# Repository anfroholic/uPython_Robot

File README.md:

Temporary home for a browser based serial terminal can be found here https://anfroholic.github.io/stache-terminal/

# Mo is live on Kickstarter!
Find more here https://www.kickstarter.com/projects/1474681136/mo-the-most-magnificent-mustached-machine 

We are the Mechanical Mustaches
FIRST® Robotics Team 8122

this is Mo the mini_mustache robotic car

Mo Dance for the FIRST Time!

Mo designed by our very own Olivia

Coming soon! Carl the Controller

here is a race put on by our amazing lead progammer Angie!!

Still in development but some previews are:

Mo hosts webpages to edit himself
## Homepage

## Live coding REPL like code terminal

## Stachboard
Dashboard is autopopulated with motors, servos, agents and many other inputs and outputs that are created

## Mo also has an editor where you can edit your own code

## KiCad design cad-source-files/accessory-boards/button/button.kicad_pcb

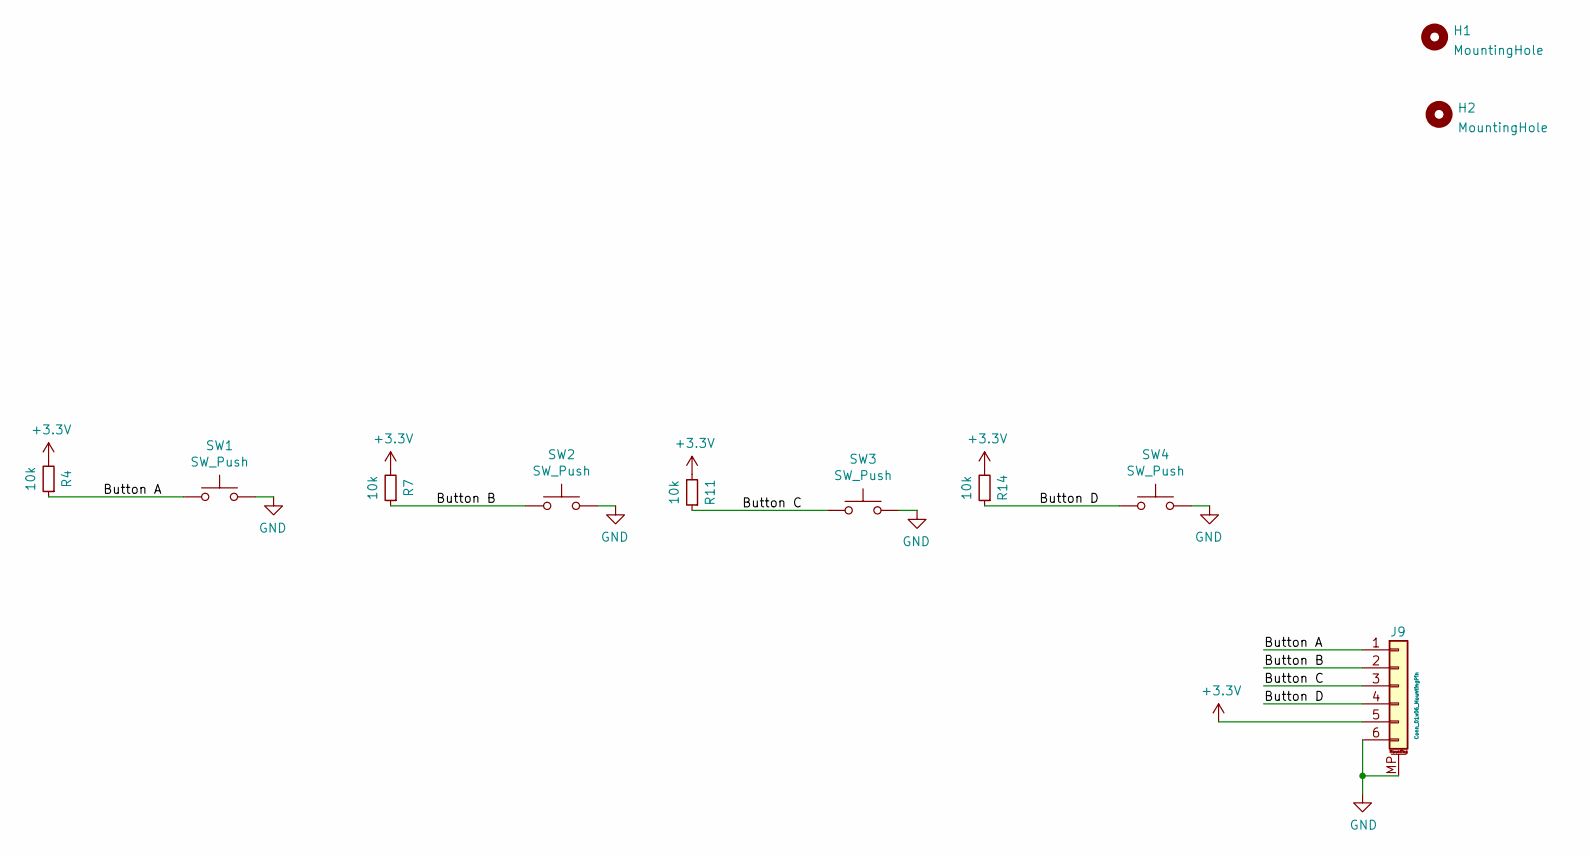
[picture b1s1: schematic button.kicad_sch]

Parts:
H1, H2: MountingHole; MountingHole_3.2mm_M3_ISO14580
J9: Conn_01x06_MountingPin; TE_84952-6_1x06-1MP_P1.0mm_Horizontal
R4, R7, R11, R14: 10k; R_0603_1608Metric
SW1, SW2, SW3, SW4: SW_Push; SWITCH_2x3_SMD_TACTILE_GREEN

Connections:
+3V3: J9.5, R4.2, R7.2, R11.2, R14.2
/Button A: J9.1, R4.1, SW1.1
/Button B: J9.2, R7.1, SW2.1
/Button C: J9.3, R11.1, SW3.1
/Button D: J9.4, R14.1, SW4.1
GND: J9.6, J9.MP (MountPin), SW1.2, SW2.2, SW3.2, SW4.2

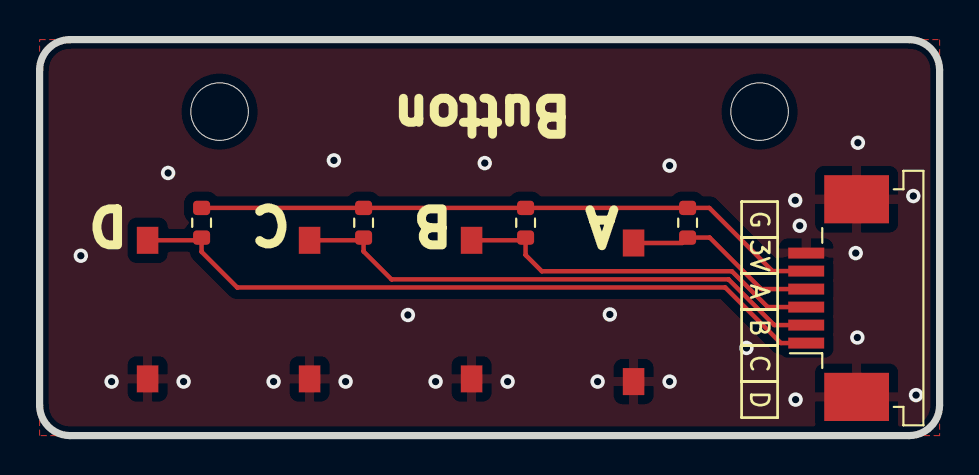
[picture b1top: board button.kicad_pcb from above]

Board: 2 copper layers, 50.0 x 22.0 mm, 11 parts (0 on the bottom side), 6 nets.

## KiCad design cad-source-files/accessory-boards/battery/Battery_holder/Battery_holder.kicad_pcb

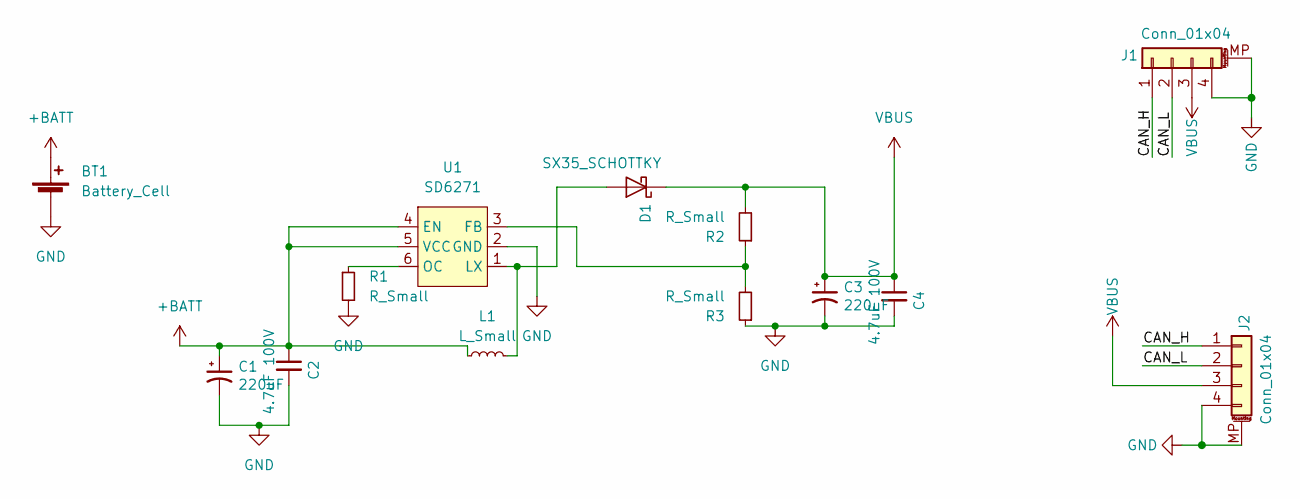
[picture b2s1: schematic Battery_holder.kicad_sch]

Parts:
BT1: Battery_Cell; 18650_holder
C1, C3: 220uF; CP_Elec_10x10.5
C2, C4: 4.7uF 100V; C_0805_2012Metric
D1: SX35_SCHOTTKY; D_SMA
J1, J2: Conn_01x04; JST_PH_S4B-PH-SM4-TB_1x04-1MP_P2.00mm_Horizontal
L1: L_Small; INDUCTOR_4.7uH_SMALL
R1, R2, R3: R_Small; R_0603_1608Metric
U1: SD6271; SOT-23-6

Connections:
+BATT: BT1.1 (+), C1.1, C2.1, L1.1, U1.4 (EN), U1.5 (VCC)
/CAN_H: J1.1, J2.1
/CAN_L: J1.2, J2.2
GND: BT1.2 (-), C1.2, C2.2, C3.2, C4.2, J1.4, J1.MP (MountPin), J2.4, J2.MP (MountPin), R1.2, R3.1, U1.2 (GND)
unnamed: D1.2 (A), L1.2, U1.1 (LX)
unnamed: R2.1, R3.2, U1.3 (FB)
unnamed: R1.1, U1.6 (OC)
VBUS: C3.1, C4.1, D1.1 (K), J1.3, J2.3, R2.2

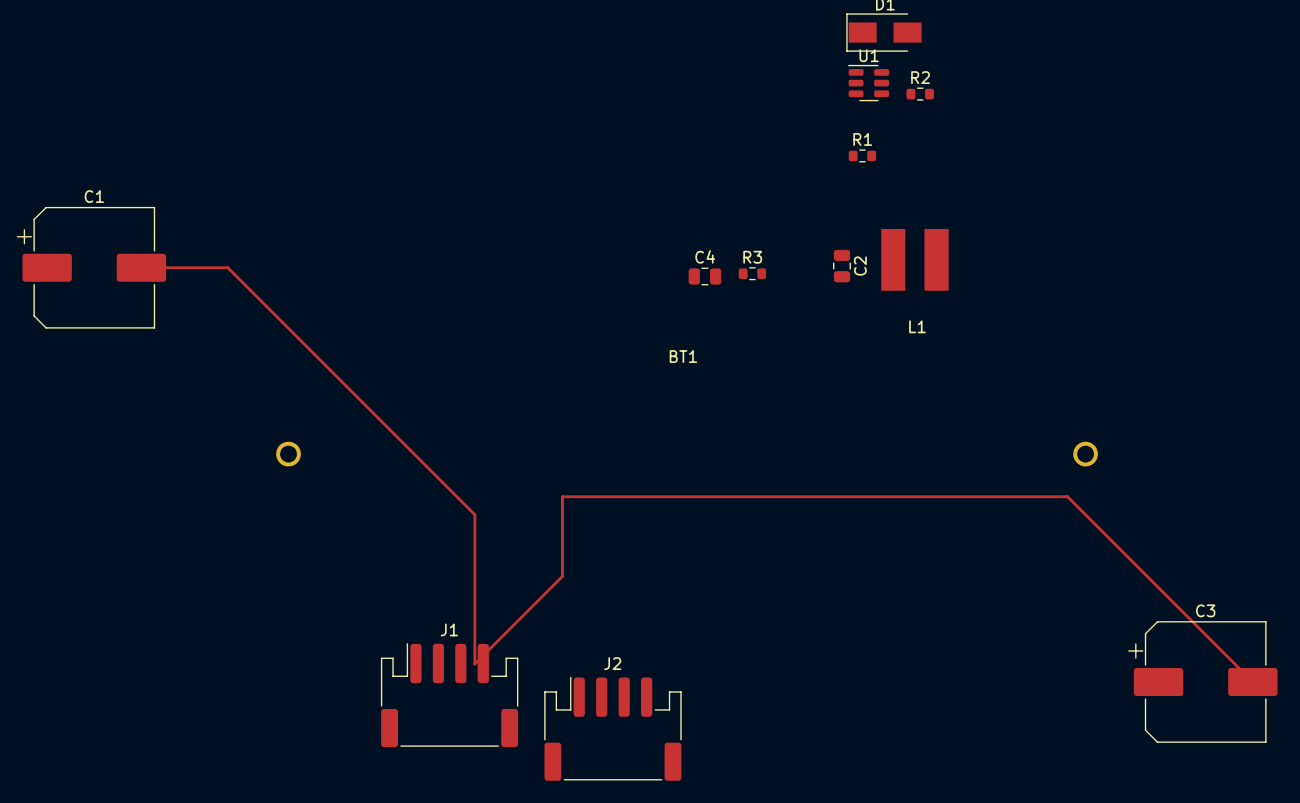
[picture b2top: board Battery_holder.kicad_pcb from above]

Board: 2 copper layers, 13 parts (0 on the bottom side), 8 nets.

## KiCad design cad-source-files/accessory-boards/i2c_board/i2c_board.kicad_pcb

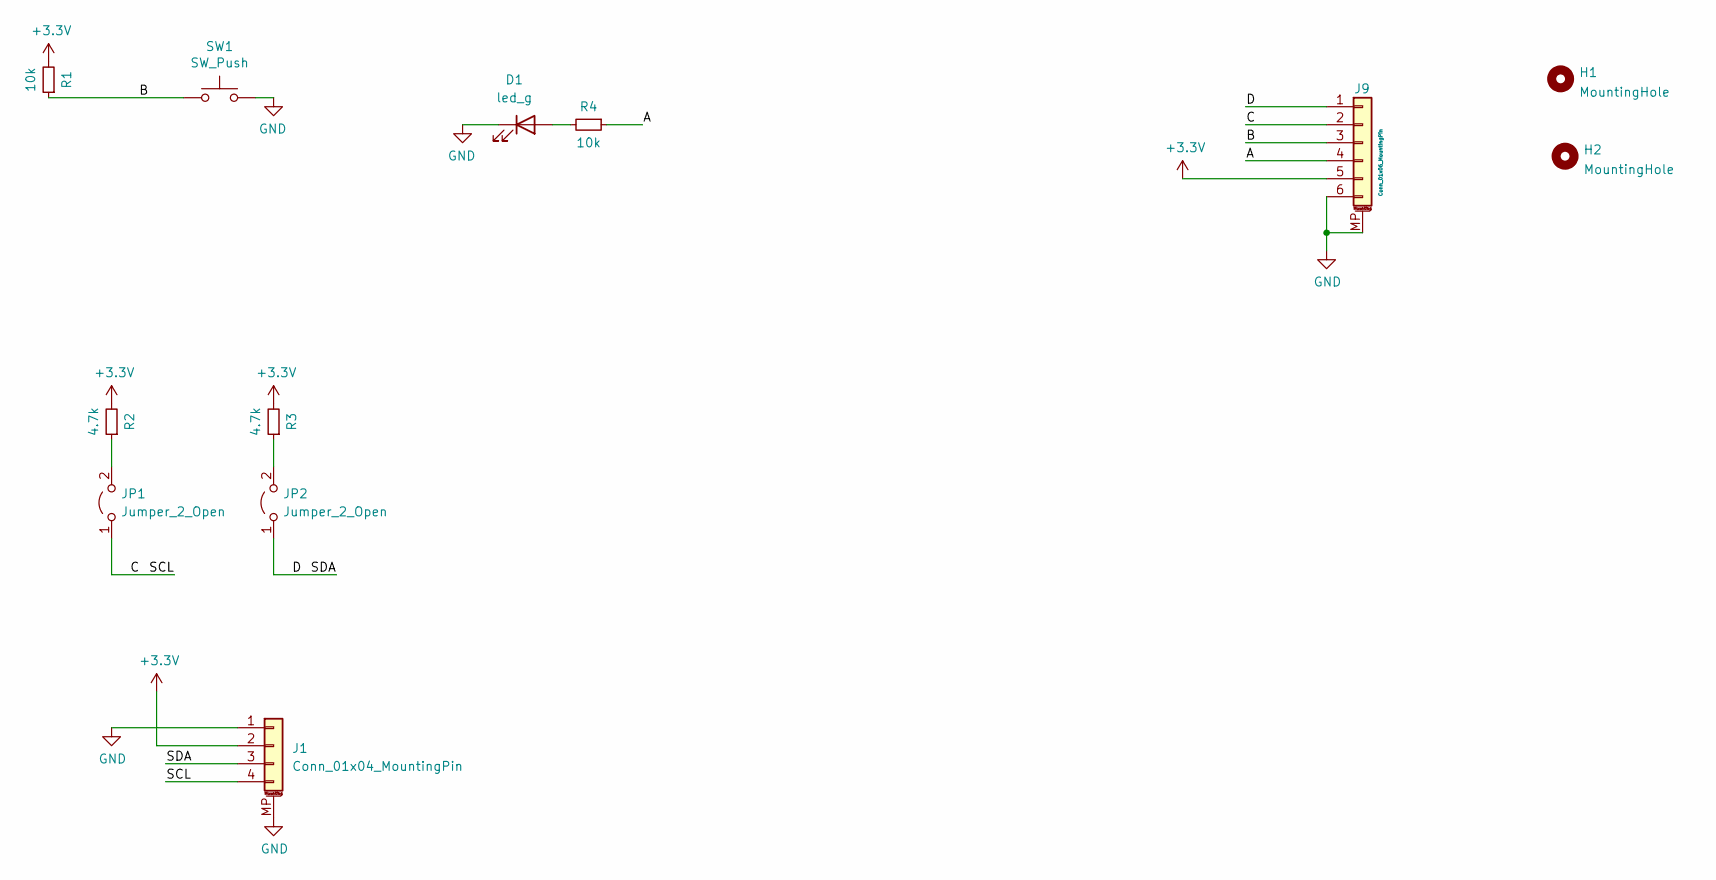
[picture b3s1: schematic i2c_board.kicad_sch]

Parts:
D1: led_g; LED_0603_1608Metric
H1, H2: MountingHole; MountingHole_3.2mm_M3_ISO14580
J1: Conn_01x04_MountingPin; JST_SH_SM04B-SRSS-TB_1x04-1MP_P1.00mm_Horizontal
J9: Conn_01x06_MountingPin; TE_84952-6_1x06-1MP_P1.0mm_Horizontal
JP1, JP2: Jumper_2_Open; SolderJumper-2_P1.3mm_Bridged_RoundedPad1.0x1.5mm
R1, R4: 10k; R_0603_1608Metric
R2, R3: 4.7k; R_0603_1608Metric
SW1: SW_Push; SWITCH_2x3_SMD_TACTILE_GREEN

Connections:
+3V3: J1.2, J9.5, R1.2, R2.2, R3.2
/A: J9.4, R4.1
/B: J9.3, R1.1, SW1.1
/C: J1.4, J9.2, JP1.1 (A)
/D: J1.3, J9.1, JP2.1 (A)
GND: D1.1 (K), J1.1, J1.MP (MountPin), J9.6, J9.MP (MountPin), SW1.2
unnamed: D1.2 (A), R4.2
unnamed: JP1.2 (B), R2.1
unnamed: JP2.2 (B), R3.1

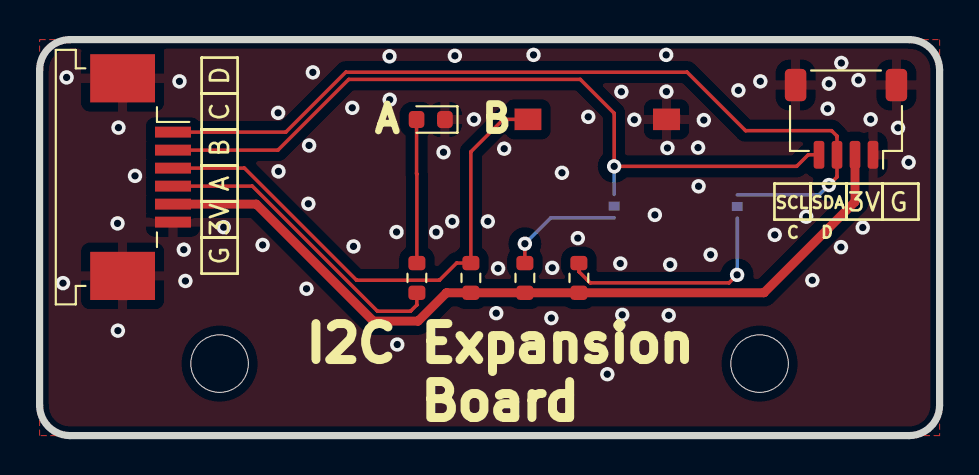
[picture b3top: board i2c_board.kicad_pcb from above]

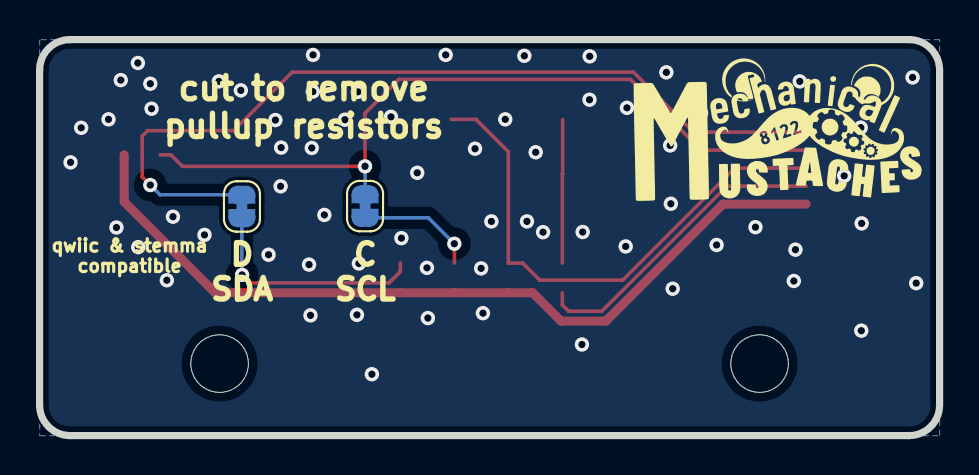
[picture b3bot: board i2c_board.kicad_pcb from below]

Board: 2 copper layers, 50.0 x 22.0 mm, 12 parts (2 on the bottom side), 9 nets.

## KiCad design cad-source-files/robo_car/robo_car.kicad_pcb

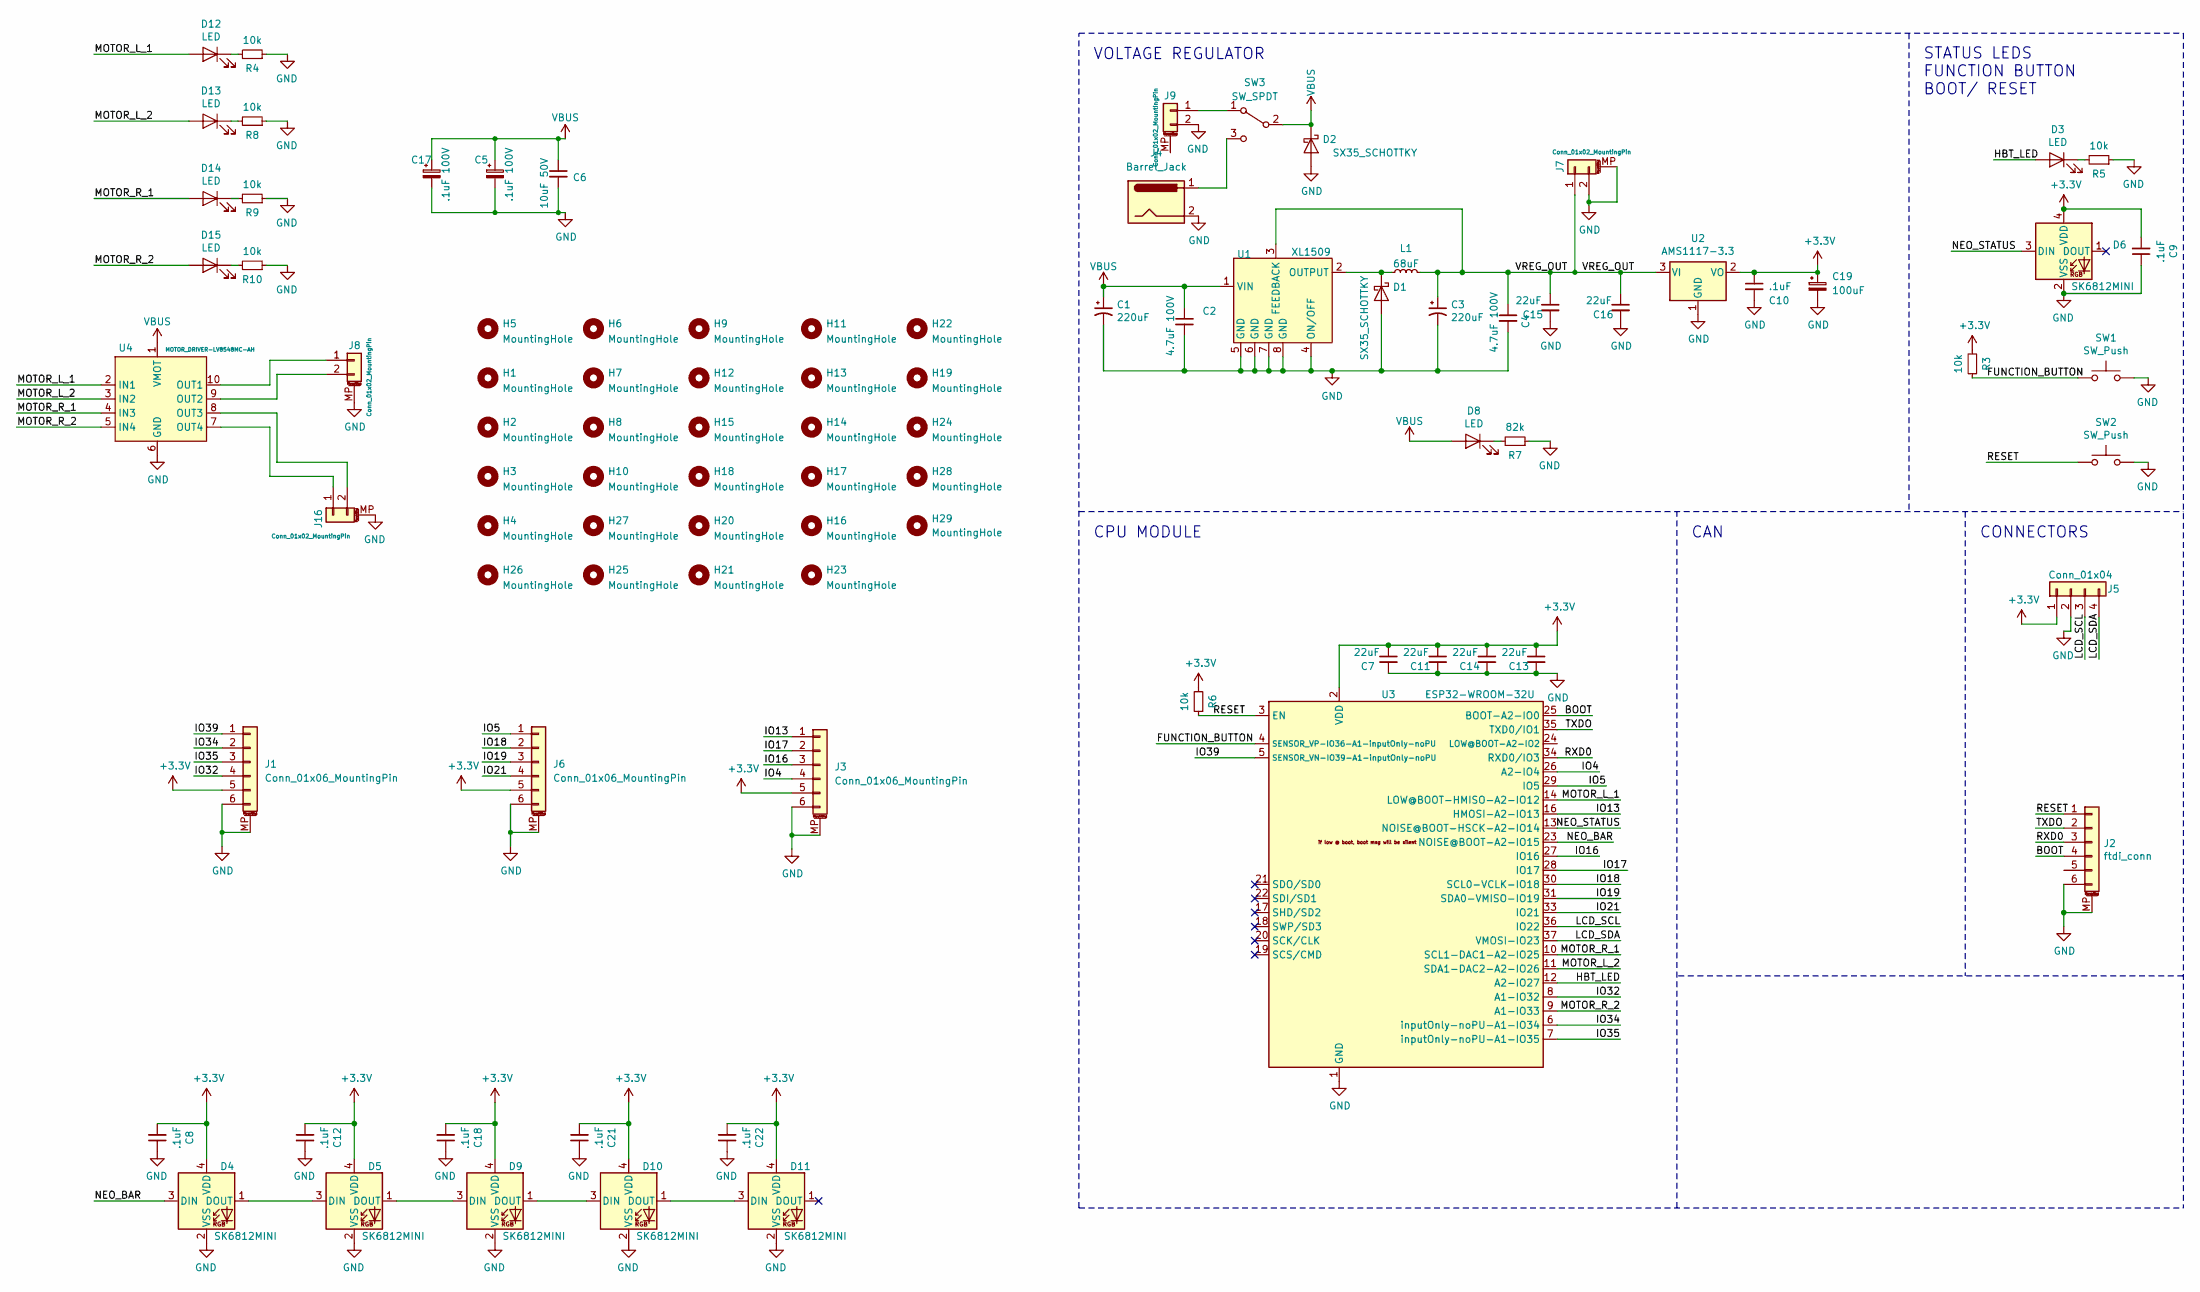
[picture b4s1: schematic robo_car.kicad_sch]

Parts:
C1, C3: 220uF; CP_Elec_10x10.5
C2, C4: 4.7uF 100V; C_0805_2012Metric
C5, C17: .1uF 100V; C_0805_2012Metric
C6: 10uF 50V; C_1206_3216Metric
C7, C11, C13, C14, C15, C16: 22uF; C_0805_2012Metric
C8, C9, C10, C12, C18, C21, C22: .1uF; C_0603_1608Metric
C19: 100uF; CP_EIA-3528-21_Kemet-B
D1, D2: SX35_SCHOTTKY; D_SMA
D3, D8, D12, D13, D14, D15: LED; LED_0603_1608Metric
D4, D5, D6, D9, D10, D11: SK6812MINI; LED_SK6812MINI_PLCC4_3.5x3.5mm_P1.75mm
H1, H2, H3, H4, H5, H6, H7, H8, H9, H10, H11, H12, H13, H14, H15, H16, H17, H18, H19, H20, H25, H26, H27, H28, H29: MountingHole; MountingHole_3.2mm_M3_ISO14580
H21, H22, H23, H24: MountingHole; MountingHole_2.7mm_M2.5_ISO14580
J1, J3, J6: Conn_01x06_MountingPin; TE_84952-6_1x06-1MP_P1.0mm_Horizontal
J2: ftdi_conn; JST_SH_SM06B-SRSS-TB_1x06-1MP_P1.00mm_Horizontal
J4: Barrel_Jack; BarrelJack_Horizontal
J5: Conn_01x04; PinSocket_1x04_P2.54mm_Vertical
J7: Conn_01x02_MountingPin; JST_PH_B2B-PH-K_1x02_P2.00mm_Vertical
J8, J16: Conn_01x02_MountingPin; JST_PH_S2B-PH-K_1x02_P2.00mm_Horizontal
J9: Conn_01x02_MountingPin; JST_XH_B2B-XH-AM_1x02_P2.50mm_Vertical
L1: 68uF; INDUCTOR-68uH
R3, R4, R5, R6, R8, R9, R10: 10k; R_0603_1608Metric
R7: 82k; R_0603_1608Metric
SW1, SW2: SW_Push; SWITCH_2x3_SMD_TACTILE_GREEN
SW3: SW_SPDT; SW_SLIDE_SS-12D10L9
U1: XL1509; SOIC-8_3.9x4.9mm_P1.27mm
U2: AMS1117-3.3; SOT-223-3_TabPin2
U3: ESP32-WROOM-32U; ESP32-WROOM-32U_evezor
U4: MOTOR_DRIVER-LV8548MC-AH; SOIC-10_LV8548MC-AH_evezor

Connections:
+3V3: C7.1, C8.2, C9.2, C10.1, C11.1, C12.2, C13.1, C14.1, C18.2, C19.1, C21.2, C22.2, D4.4 (VDD), D5.4 (VDD), D6.4 (VDD), D9.4 (VDD), D10.4 (VDD), D11.4 (VDD), J1.5, J3.5, J5.1, J6.5, R3.2, R6.2, U2.2 (VO), U3.2 (VDD); also elsewhere on the board
/BOOT: J2.4, U3.25 (BOOT-A2-IO0)
/FUNCTION_BUTTON: R3.1, SW1.1, U3.4 (SENSOR_VP-IO36-A1-inputOnly-noPU)
/HBT_LED: D3.2 (A), U3.12 (A2-IO27)
/IO4: J3.4, U3.26 (A2-IO4)
/IO5: J6.1, U3.29 (IO5)
/IO13: J3.1, U3.16 (HMOSI-A2-IO13)
/IO16: J3.3, U3.27 (IO16)
/IO17: J3.2, U3.28 (IO17)
/IO18: J6.2, U3.30 (SCL0-VCLK-IO18)
/IO19: J6.3, U3.31 (SDA0-VMISO-IO19)
/IO21: J6.4, U3.33 (IO21)
/IO32: J1.4, U3.8 (A1-IO32)
/IO34: J1.2, U3.6 (inputOnly-noPU-A1-IO34)
/IO35: J1.3, U3.7 (inputOnly-noPU-A1-IO35)
/IO39: J1.1, U3.5 (SENSOR_VN-IO39-A1-inputOnly-noPU)
/LCD_SCL: J5.3, U3.36 (IO22)
/LCD_SDA: J5.4, U3.37 (VMOSI-IO23)
/MOTOR_L_1: D12.2 (A), U3.14 (LOW@BOOT-HMISO-A2-IO12), U4.2 (IN1)
/MOTOR_L_2: D13.2 (A), U3.11 (SDA1-DAC2-A2-IO26), U4.3 (IN2)
/MOTOR_R_1: D14.2 (A), U3.10 (SCL1-DAC1-A2-IO25), U4.4 (IN3)
/MOTOR_R_2: D15.2 (A), U3.9 (A1-IO33), U4.5 (IN4)
/NEO_BAR: D4.3 (DIN), U3.23 (NOISE@BOOT-A2-IO15)
/NEO_STATUS: D6.3 (DIN), U3.13 (NOISE@BOOT-HSCK-A2-IO14)
/RESET: J2.1, R6.1, SW2.1, U3.3 (EN)
/RXD0: J2.3, U3.34 (RXD0/IO3)
/TXDO: J2.2, U3.35 (TXD0/IO1)
/VREG_OUT: C3.1, C4.1, C15.1, C16.1, J7.1, L1.1, U1.3 (FEEDBACK), U2.3 (VI)
GND: C1.2, C2.2, C3.2, C4.2, C5.2, C6.2, C7.2, C8.1, C9.1, C10.2, C11.2, C12.1, C13.2, C14.2, C15.2, C16.2, C17.2, C18.1, C19.2, C21.1, C22.1, D1.2 (A), D2.2 (A), D4.2 (VSS), D5.2 (VSS), D6.2 (VSS), D9.2 (VSS), D10.2 (VSS), D11.2 (VSS), J1.6, J1.MP (MountPin), J2.6, J2.MP (MountPin), J3.6, J3.MP (MountPin), J4.2, J5.2, J6.6, J6.MP (MountPin), J7.2, J7.MP (MountPin), J8.MP (MountPin), J9.2, J16.MP (MountPin), R4.1, R5.1, R7.1, R8.1, R9.1, R10.1, SW1.2, SW2.2, U1.4 (ON/OFF), U1.5 (GND), U1.6 (GND), U1.7 (GND), U1.8 (GND), U2.1 (GND), U3.1 (GND), U3.15 (GND), U3.38 (GND), U3.39 (GND), U4.6 (GND); also elsewhere on the board
unnamed: D1.1 (K), L1.2, U1.2 (OUTPUT)
unnamed: D3.1 (K), R5.2
unnamed: D4.1 (DOUT), D5.3 (DIN)
unnamed: D5.1 (DOUT), D9.3 (DIN)
unnamed: D8.1 (K), R7.2
unnamed: D10.1 (DOUT), D11.3 (DIN)
unnamed: D9.1 (DOUT), D10.3 (DIN)
unnamed: D12.1 (K), R4.2
unnamed: D13.1 (K), R8.2
unnamed: D14.1 (K), R9.2
unnamed: D15.1 (K), R10.2
unnamed: J4.1, SW3.3 (C)
unnamed: J8.1, U4.10 (OUT1)
unnamed: J8.2, U4.9 (OUT2)
unnamed: J9.1, SW3.1 (A)
unnamed: J16.1, U4.7 (OUT4)
unnamed: J16.2, U4.8 (OUT3)
VBUS: C1.1, C2.1, C5.1, C6.1, C17.1, D2.1 (K), D8.2 (A), SW3.2 (B), U1.1 (VIN), U4.1 (VMOT)

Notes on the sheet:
VOLTAGE REGULATOR
CPU MODULE
CAN
STATUS LEDS FUNCTION BUTTON BOOT/ RESET
CONNECTORS

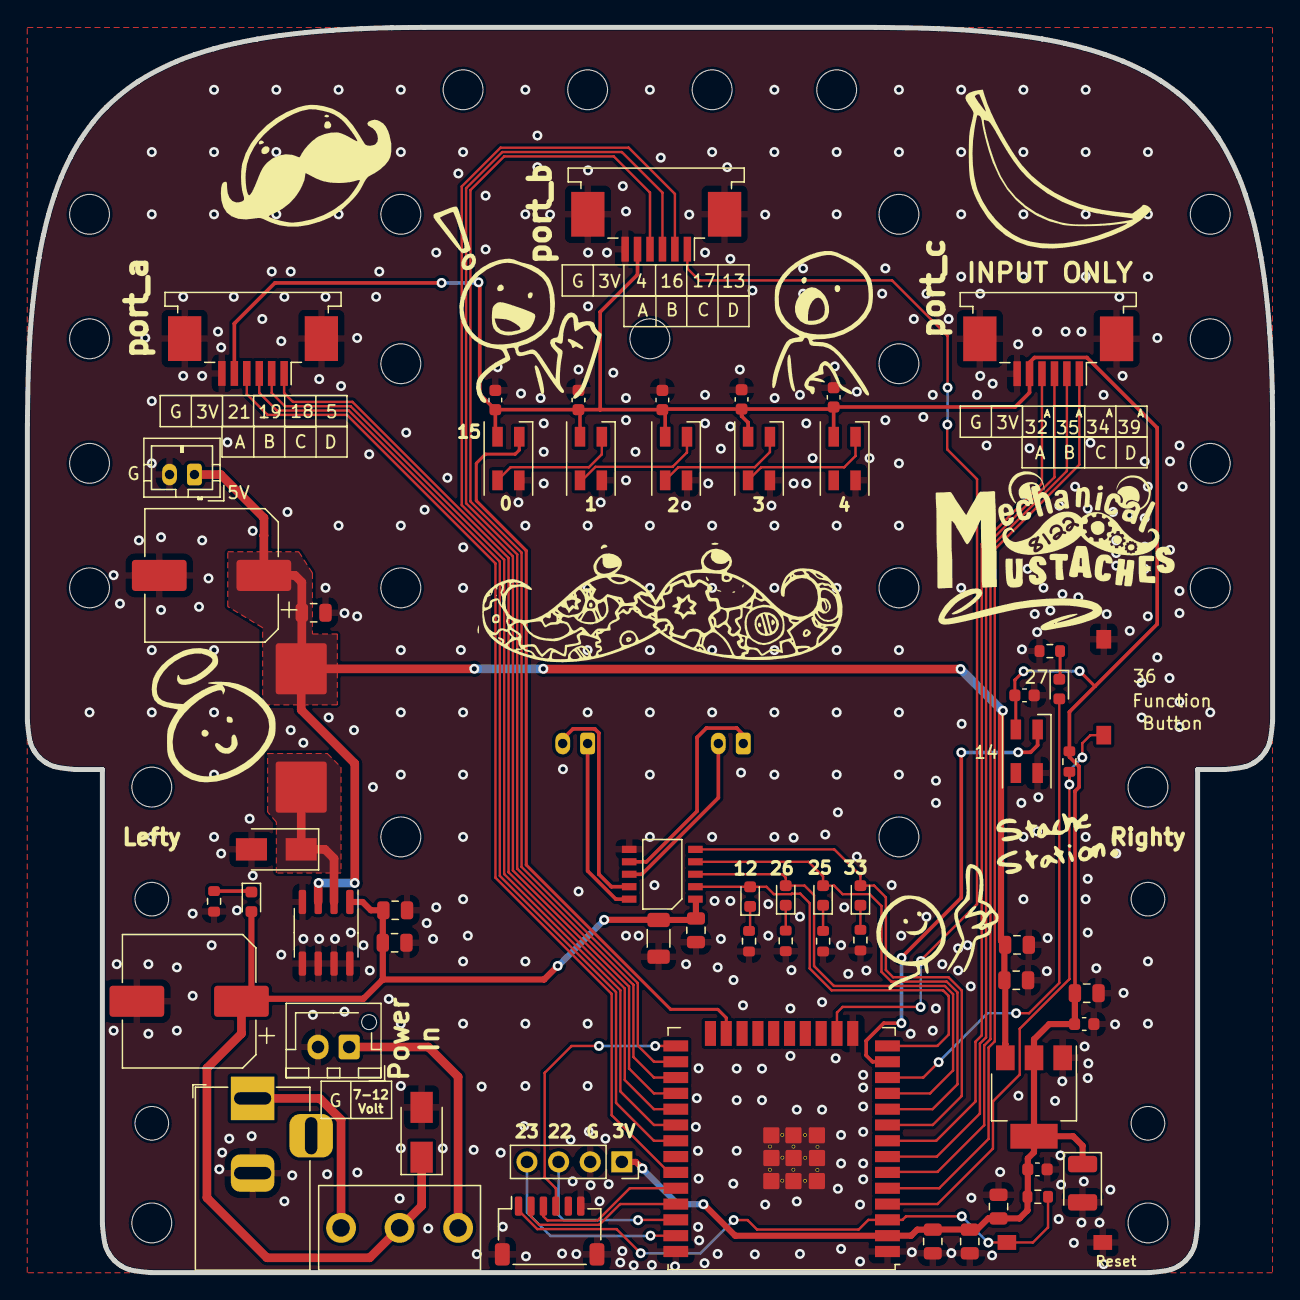
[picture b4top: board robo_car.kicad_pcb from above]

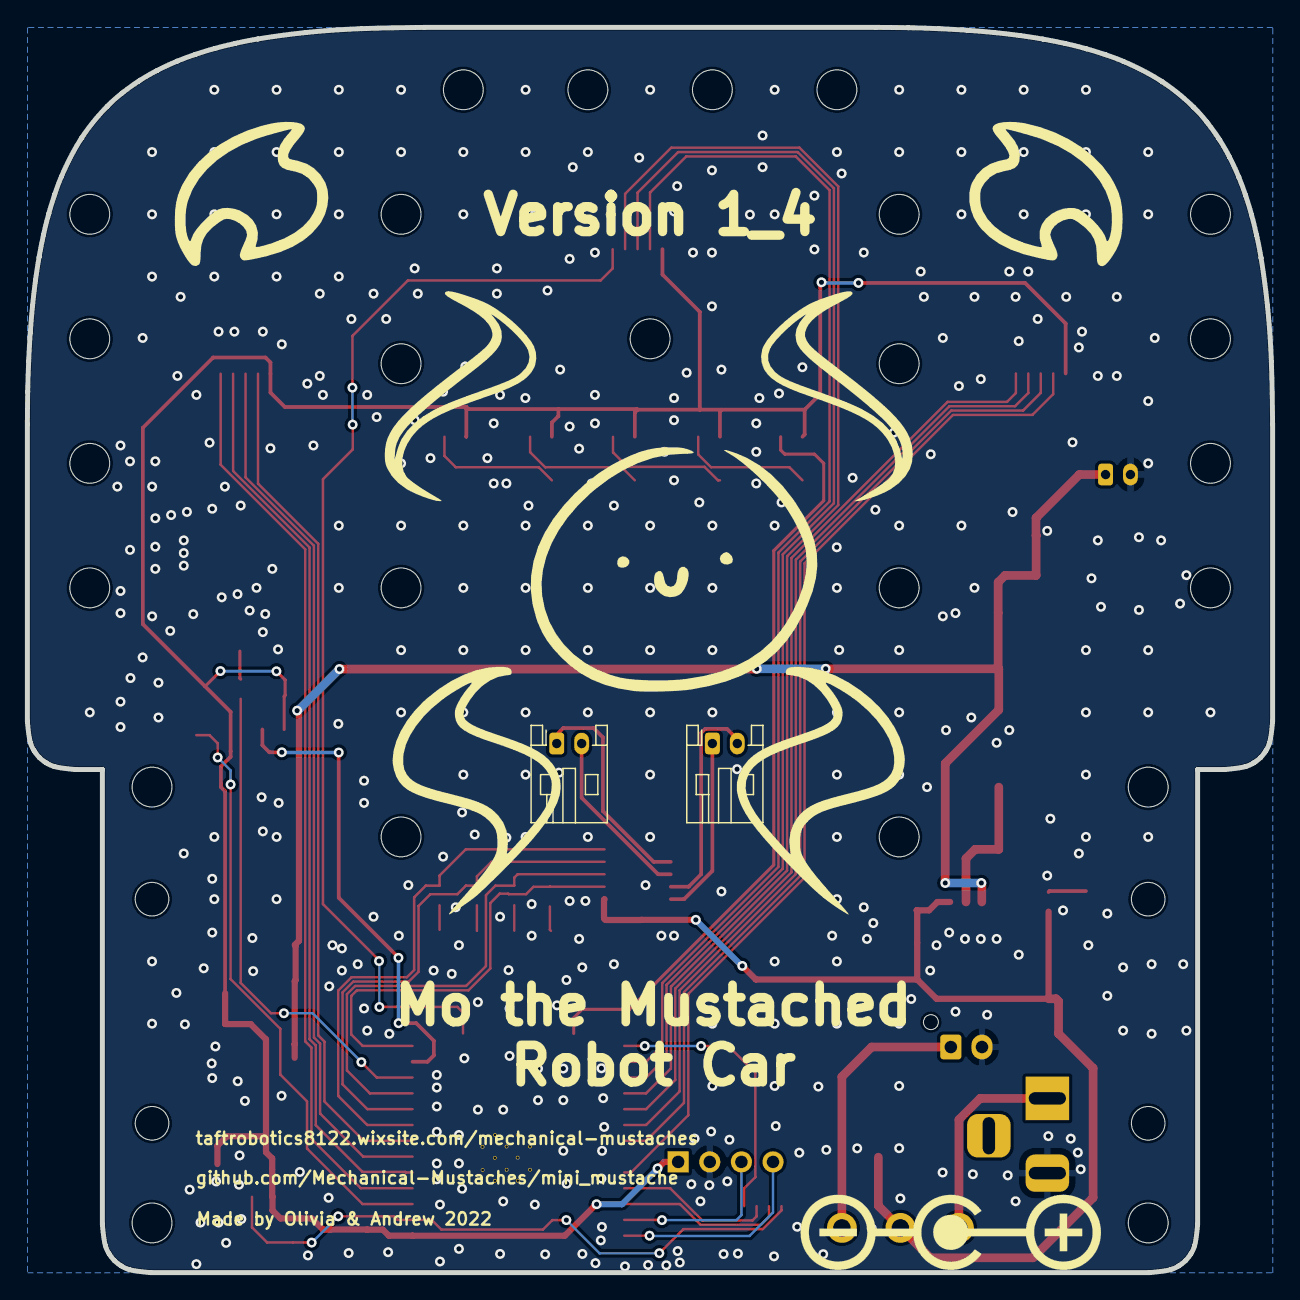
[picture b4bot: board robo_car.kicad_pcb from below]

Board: 2 copper layers, 100.0 x 100.0 mm, 91 parts (2 on the bottom side), 47 nets.

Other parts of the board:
C14#2: .1uF; C_0603_1608Metric

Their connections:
+3V3: C14#2.1; also elsewhere on the board
GND: C14#2.2; also elsewhere on the board

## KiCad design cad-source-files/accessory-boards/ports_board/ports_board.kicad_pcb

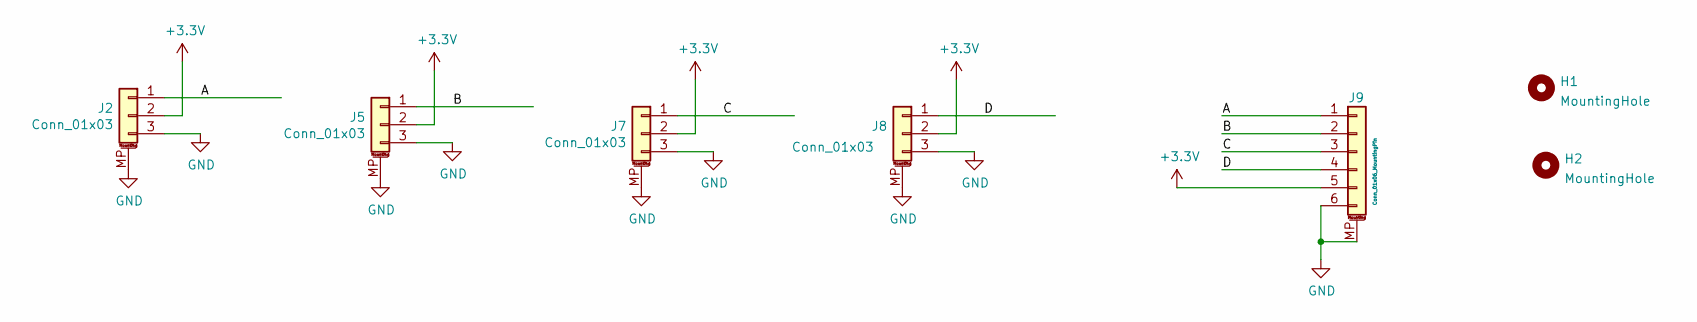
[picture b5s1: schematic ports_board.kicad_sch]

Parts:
H1, H2: MountingHole; MountingHole_3.2mm_M3_ISO14580
J2, J5, J7, J8: Conn_01x03; JST_PH_B3B-PH-SM4-TB_1x03-1MP_P2.00mm_Vertical
J9: Conn_01x06_MountingPin; TE_84952-6_1x06-1MP_P1.0mm_Horizontal

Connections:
+3V3: J2.2, J5.2, J7.2, J8.2, J9.5
/A: J2.1, J9.1
/B: J5.1, J9.2
/C: J7.1, J9.3
/D: J8.1, J9.4
GND: J2.3, J2.MP (MountPin), J5.3, J5.MP (MountPin), J7.3, J7.MP (MountPin), J8.3, J8.MP (MountPin), J9.6, J9.MP (MountPin)

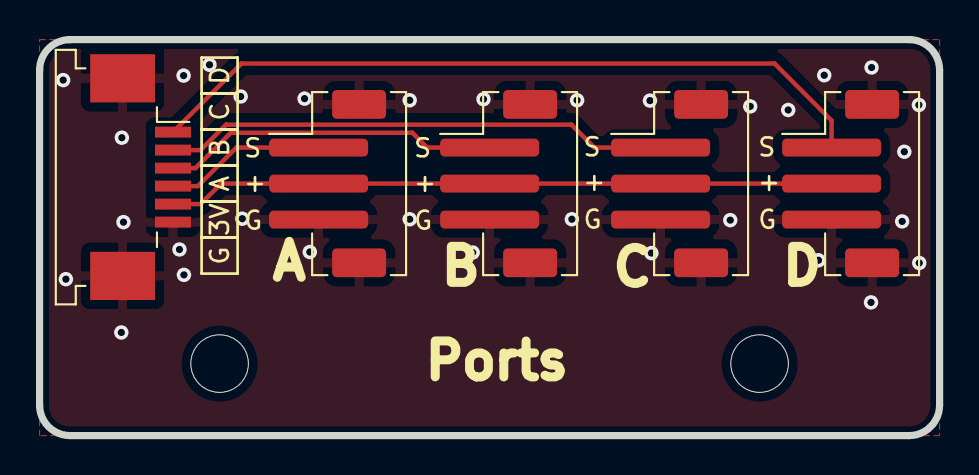
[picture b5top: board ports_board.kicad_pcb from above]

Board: 2 copper layers, 50.0 x 22.0 mm, 7 parts (0 on the bottom side), 6 nets.

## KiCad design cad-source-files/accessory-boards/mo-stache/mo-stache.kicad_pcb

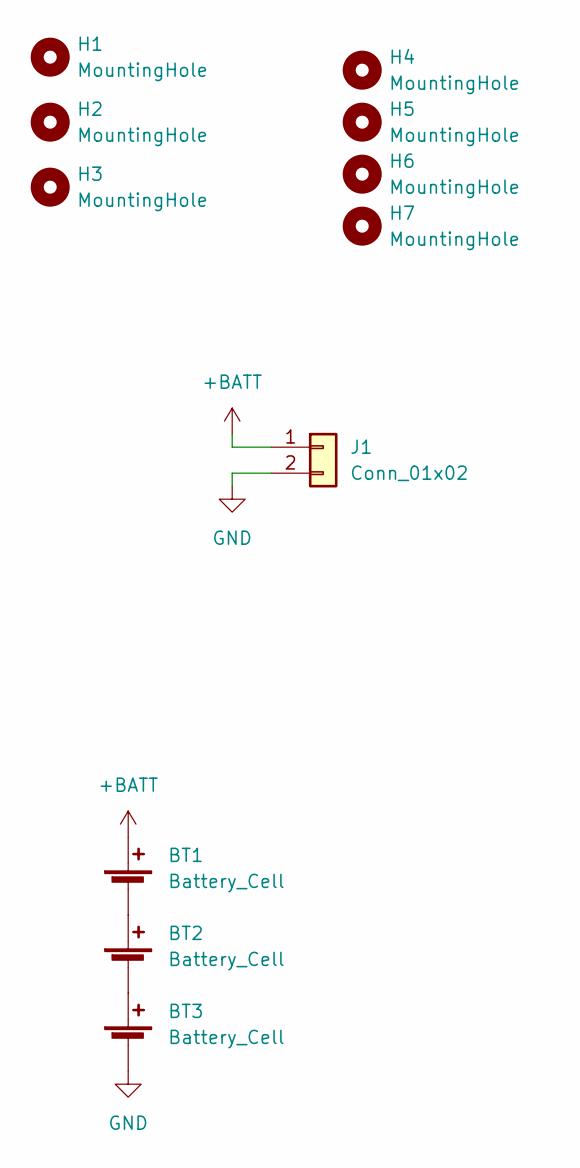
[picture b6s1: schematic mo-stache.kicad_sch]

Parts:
BT1, BT2, BT3: Battery_Cell; 16350_holder
H1, H2, H3: MountingHole; MountingHole_4.95mm_3_16in
H4, H5, H6, H7: MountingHole; MountingHole_2.7mm_M2.5_ISO7380
J1: Conn_01x02; JST_XH_B2B-XH-AM_1x02_P2.50mm_Vertical

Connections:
+BATT: BT1.1 (+), J1.1
GND: BT3.2 (-), J1.2
unnamed: BT1.2 (-), BT2.1 (+)
unnamed: BT2.2 (-), BT3.1 (+)

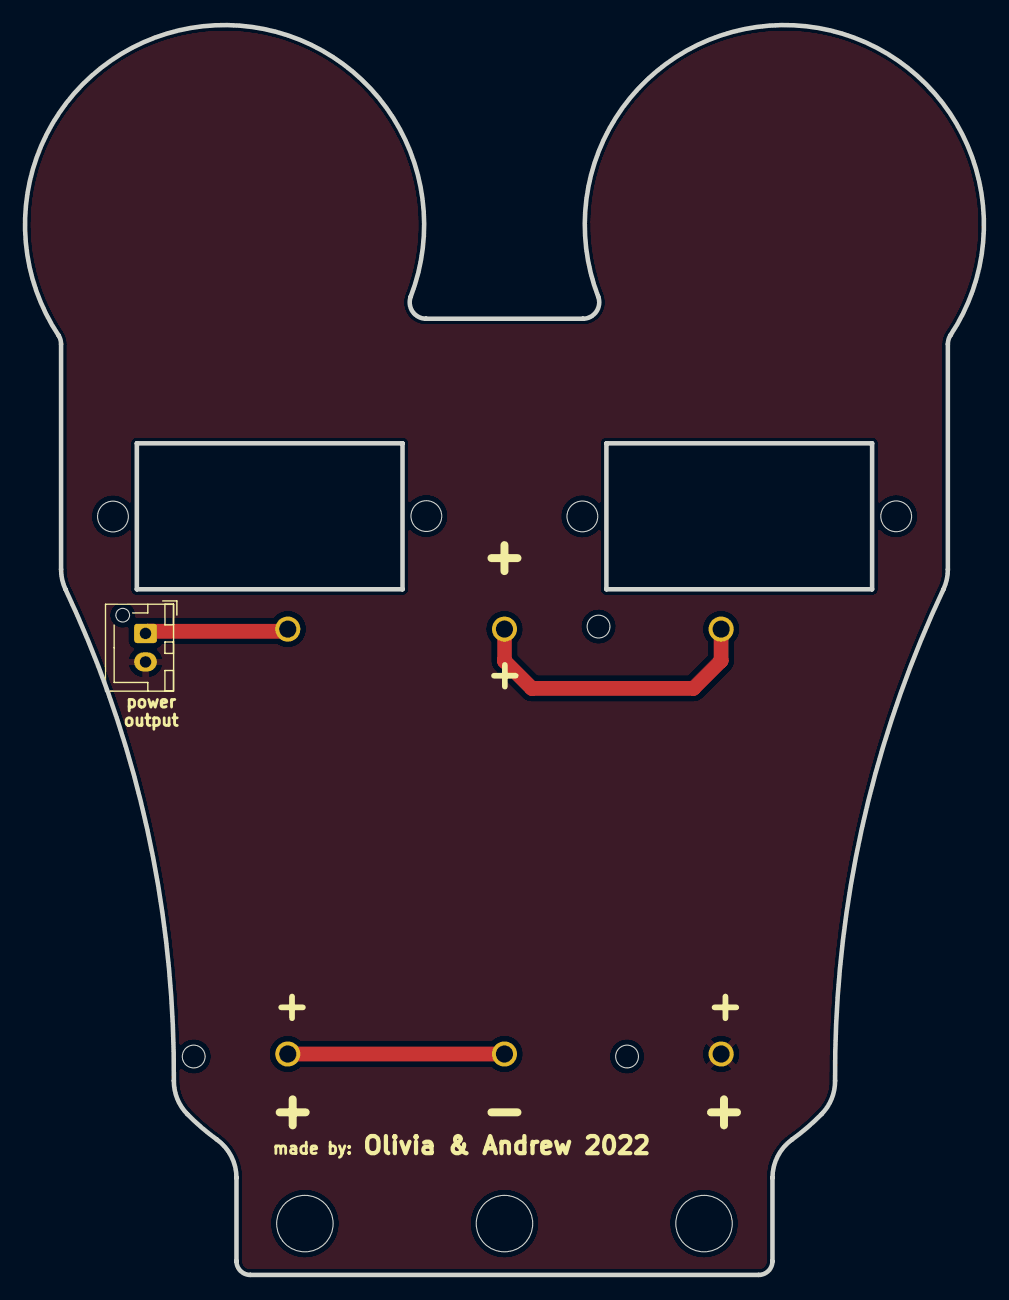
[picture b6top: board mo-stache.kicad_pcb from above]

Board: 2 copper layers, 84.1 x 109.6 mm, 11 parts (0 on the bottom side), 4 nets.
